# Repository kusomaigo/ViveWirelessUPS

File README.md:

# ViveWirelessUPS

HTC Vive Wireless UPS (Uninterruptable Power Supply)

 - Pololu U3V70A for stepping up a single 18650 cell to ~12V as a backup power source for your HTC Vive Wireless module
 - ATTiny13a for QC3.0 tricking
 - LM5050-1 OR-ing FET controller for power switching

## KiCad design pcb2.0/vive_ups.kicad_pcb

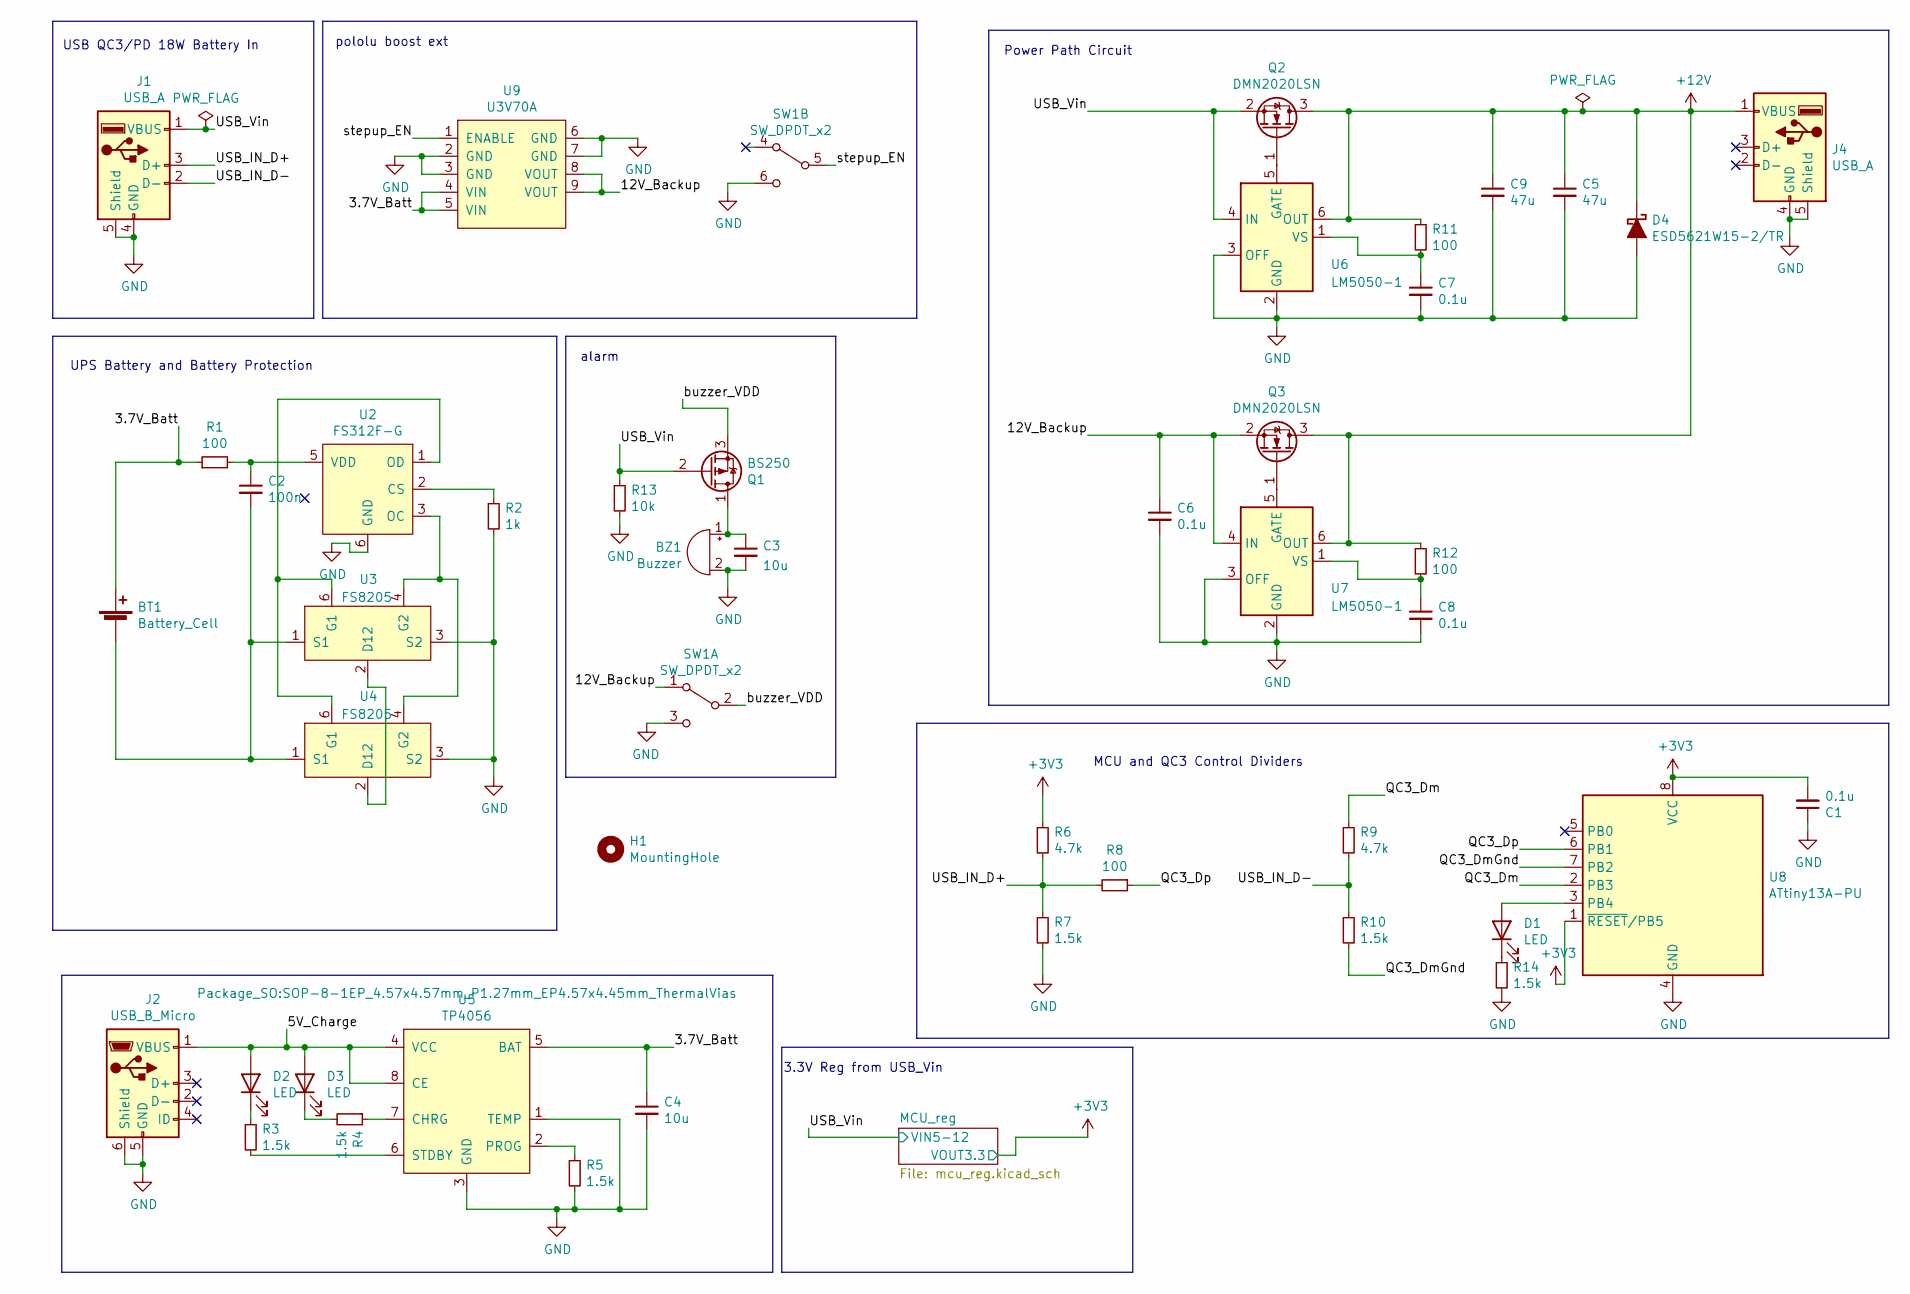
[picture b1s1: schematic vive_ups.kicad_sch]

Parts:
BT1: Battery_Cell; 18650_holder_THT
BZ1: Buzzer; PinHeader_1x02_P2.54mm_Vertical
C1, C6, C7, C8: 0.1u; C_0603_1608Metric_Pad1.08x0.95mm_HandSolder
C2: 100n; C_0603_1608Metric_Pad1.08x0.95mm_HandSolder
C3: 10u
C4: 10u; C_0603_1608Metric_Pad1.08x0.95mm_HandSolder
C5, C9: 47u; CP_Radial_D6.3mm_P2.50mm
D1, D2, D3: LED; LED_0603_1608Metric_Pad1.05x0.95mm_HandSolder
D4: ESD5621W15-2/TR; D_SOD-323_HandSoldering
H1: MountingHole; MountingHole_3.2mm_M3
J1, J4: USB_A; USB_A_Molex_67643_Horizontal
J2: USB_B_Micro; USB_Micro-B_Amphenol_10118194_Horizontal
Q1: BS250; TO-92_Inline
Q2, Q3: DMN2020LSN; SC-59_Handsoldering
R1, R8, R11, R12: 100; R_0603_1608Metric_Pad0.98x0.95mm_HandSolder
R2: 1k; R_0603_1608Metric_Pad0.98x0.95mm_HandSolder
R3, R4, R5, R7, R10, R14: 1.5k; R_0603_1608Metric_Pad0.98x0.95mm_HandSolder
R6, R9: 4.7k; R_0603_1608Metric_Pad0.98x0.95mm_HandSolder
R13: 10k; R_Axial_DIN0309_L9.0mm_D3.2mm_P5.08mm_Vertical
SW1: SW_DPDT_x2; K3-2245D-F1
U2: FS312F-G; SOT-23-6_Handsoldering
U3, U4: FS8205; SOT-23-6_Handsoldering
U5: TP4056; SOP-8-1EP_4.57x4.57mm_P1.27mm_EP4.57x4.45mm_ThermalVias
U6, U7: LM5050-1; TSOT-23-6
U8: ATtiny13A-PU; DIP-8_W7.62mm
U9: U3V70A

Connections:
+3V3: C1.2, R6.1, U8.1 (~RESET/PB5), U8.8 (VCC); also elsewhere on the board
+12V: C5.1, C9.1, D4.1 (K), J4.1 (VBUS), Q2.3 (D), Q3.3 (D), R11.1, R12.1, U6.6 (OUT), U7.6 (OUT)
/3.7V_Batt: BT1.1 (+), C4.1, R1.1, U5.5 (BAT), U9.4 (VIN), U9.5 (VIN)
/5V_Charge: D2.2 (A), D3.2 (A), J2.1 (VBUS), U5.4 (VCC), U5.8 (CE)
/12V_Backup: C6.1, Q3.2 (S), SW1.1 (A), U7.4 (IN), U9.8 (VOUT), U9.9 (VOUT)
/QC3_Dm: R9.1, U8.2 (PB3)
/QC3_DmGnd: R10.2, U8.7 (PB2)
/QC3_Dp: R8.1, U8.6 (PB1)
/USB_IN_D+: J1.3 (D+), R6.2, R7.1, R8.2
/USB_IN_D-: J1.2 (D-), R9.2, R10.1
/USB_Vin: J1.1 (VBUS), Q1.2 (G), Q2.2 (S), R13.1, U6.4 (IN); also elsewhere on the board
/buzzer_VDD: Q1.3 (S), SW1.2 (B)
/stepup_EN: SW1.5 (B), U9.1 (ENABLE)
GND: BZ1.2 (+), C1.1, C3.2 (+), C4.2, C5.2, C6.2, C7.2, C8.2, C9.2, D4.2 (A), J1.4 (GND), J1.5 (Shield), J2.5 (GND), J2.6 (Shield), J4.4 (GND), J4.5 (Shield), R2.2, R5.2, R7.2, R13.2, R14.2, SW1.3 (C), SW1.6 (C), U2.6 (GND), U3.3 (S2), U4.3 (S2), U5.1 (TEMP), U5.3 (GND), U5.9 (THERMAL), U6.2 (GND), U6.3 (OFF), U7.2 (GND), U7.3 (OFF), U8.4 (GND), U9.2 (GND), U9.3 (GND), U9.6 (GND), U9.7 (GND); also elsewhere on the board
unnamed: BT1.2 (-), C2.2, U3.1 (S1), U4.1 (S1)
unnamed: BZ1.1 (-), C3.1 (-), Q1.1 (D)
unnamed: C2.1, R1.2, U2.5 (VDD)
unnamed: C7.1, R11.2, U6.1 (VS)
unnamed: C8.1, R12.2, U7.1 (VS)
unnamed: D1.1 (K), R14.1
unnamed: D1.2 (A), U8.3 (PB4)
unnamed: D2.1 (K), R3.1
unnamed: D3.1 (K), R4.2
unnamed: Q2.1 (G), U6.5 (GATE)
unnamed: Q3.1 (G), U7.5 (GATE)
unnamed: R2.1, U2.2 (CS)
unnamed: R3.2, U5.6 (STDBY)
unnamed: R4.1, U5.7 (CHRG)
unnamed: R5.1, U5.2 (PROG)
unnamed: U2.1 (OD), U3.6 (G1), U4.6 (G1)
unnamed: U2.3 (OC), U3.4 (G2), U4.4 (G2)
unnamed: U3.2 (D12), U4.2 (D12)

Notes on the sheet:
USB QC3/PD 18W Battery In
UPS Battery and Battery Protection
pololu boost ext
alarm
3.3V Reg from USB_Vin
Power Path Circuit
MCU and QC3 Control Dividers

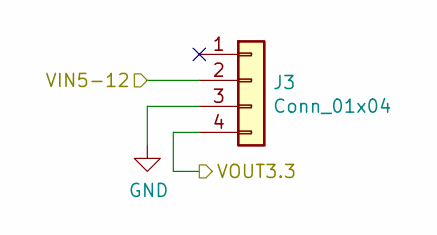
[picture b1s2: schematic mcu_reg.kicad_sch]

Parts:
J3: Conn_01x04; PinHeader_1x04_P2.54mm_Vertical

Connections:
+3V3: J3.4; also elsewhere on the board
/USB_Vin: J3.2; also elsewhere on the board
GND: J3.3; also elsewhere on the board

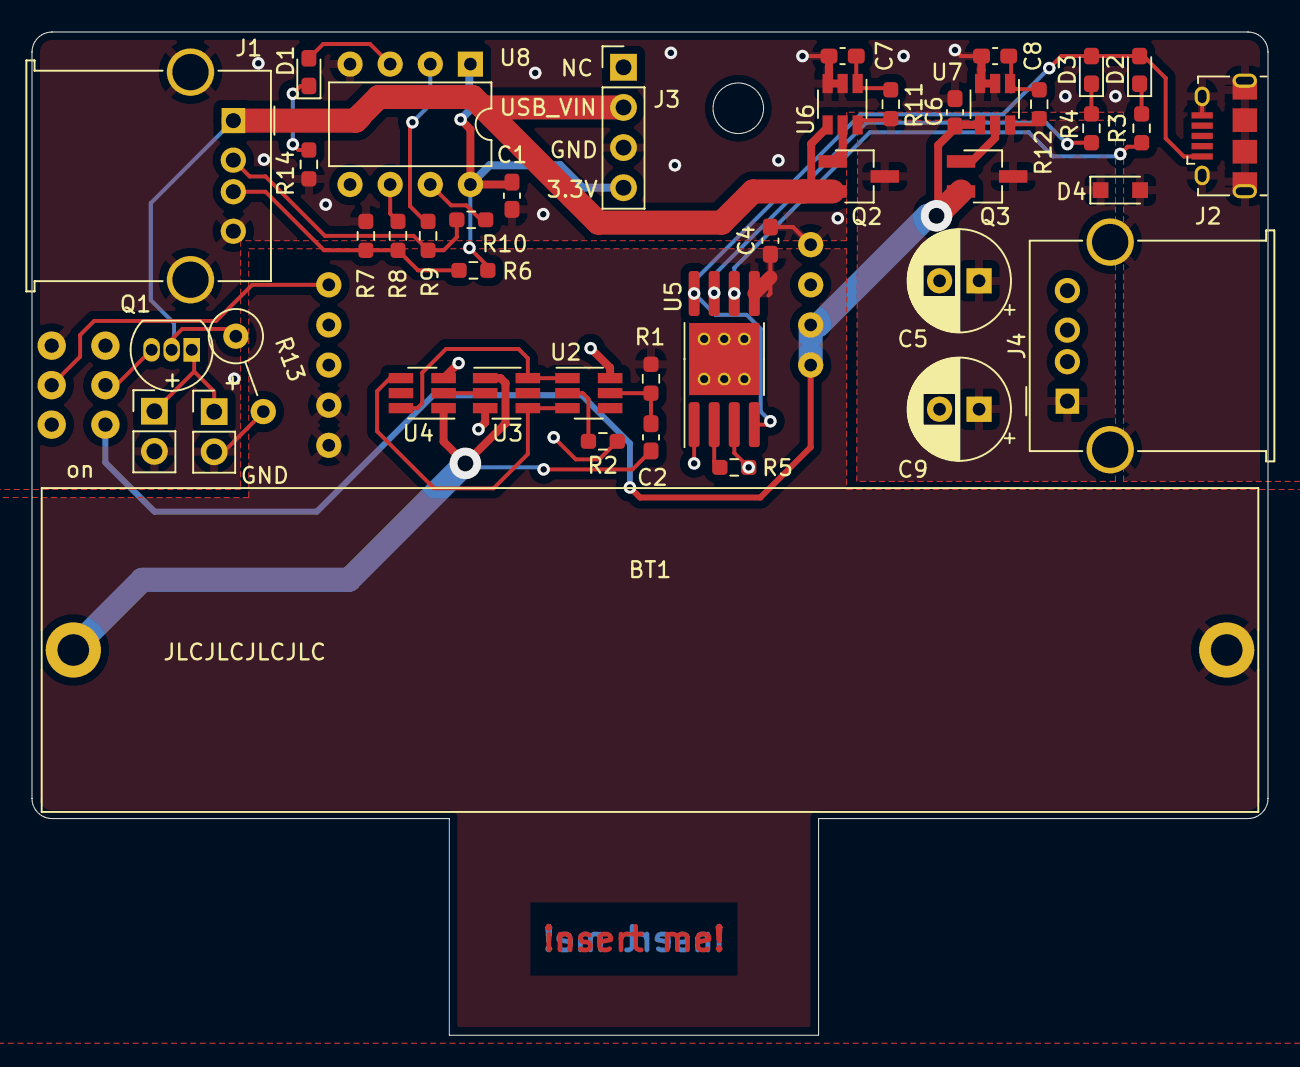
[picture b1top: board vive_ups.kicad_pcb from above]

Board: 2 copper layers, 78.2 x 63.5 mm, 46 parts (0 on the bottom side), 32 nets.

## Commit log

2021-06-04 6/3 create public project repo
2021-06-13 swapped buzzer transistor to equivalent fet (oops)
2022-04-01 properly functioning design in pcb2.0 folder
